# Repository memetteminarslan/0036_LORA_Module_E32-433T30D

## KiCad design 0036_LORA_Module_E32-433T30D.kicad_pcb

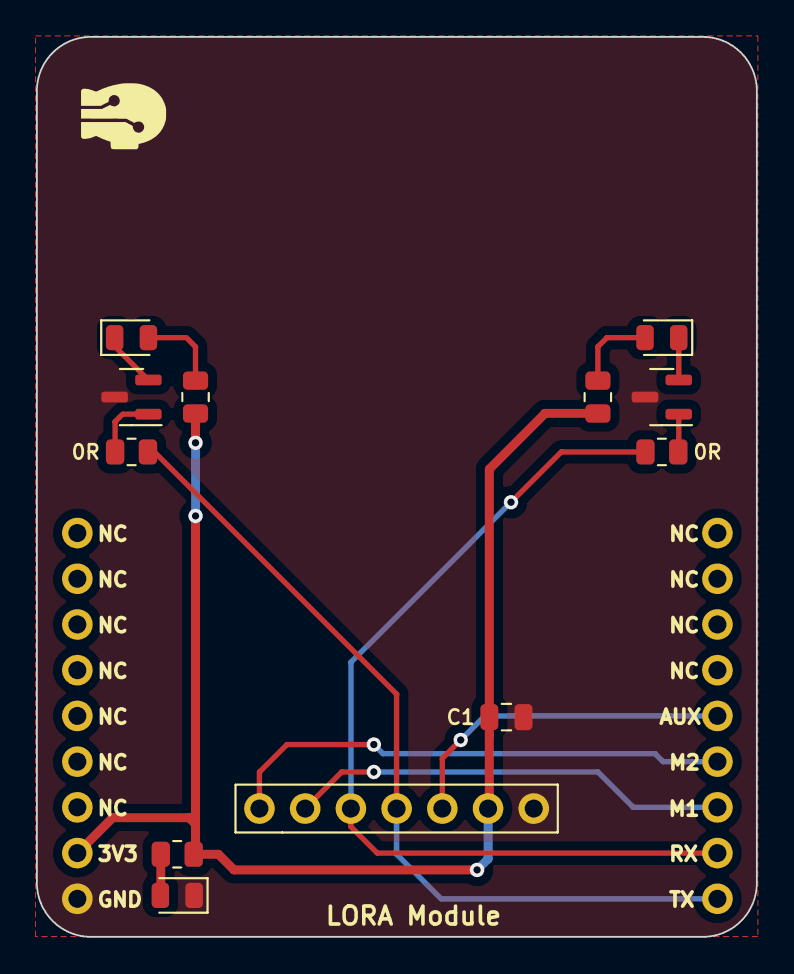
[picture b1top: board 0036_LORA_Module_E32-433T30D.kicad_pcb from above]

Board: 2 copper layers, 40.0 x 50.0 mm, 13 parts (0 on the bottom side), 14 nets.

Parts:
0R, 0R#2: 0r; R_0805_2012Metric
C1: C; C_0805_2012Metric
D1, D2, D4: LED; LED_0805_2012Metric
J1: Conn_01x07_Pin; PinHeader_1x07_P2.54mm_Vertical
Q1: MMBT3906; SOT-23
Q2: 3906; SOT-23
R1, R2, R7: R; R_0805_2012Metric
U1: pin_header_5-3

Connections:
+3V3: C1.1, J1.6 (VCC), R1.1, R2.1, R7.2, U1.8
AUX: J1.5 (AUX), U1.14
GND: C1.2, D4.1 (K), J1.7 (GND), Q1.3 (C), Q2.3 (C), U1.9
M1: J1.2 (M1), U1.12
M2: J1.1 (M0), U1.13
unnamed: D1.2 (A), R1.2
unnamed: D1.1 (K), Q1.2 (E)
unnamed: D2.2 (A), R2.2
unnamed: D2.1 (K), Q2.2 (E)
unnamed: D4.2 (A), R7.1
unnamed: 0R.1, Q1.1 (B)
unnamed: 0R#2.1, Q2.1 (B)
RX: 0R#2.2, J1.3 (RX), U1.11
TX: 0R.2, J1.4 (TX), U1.10
